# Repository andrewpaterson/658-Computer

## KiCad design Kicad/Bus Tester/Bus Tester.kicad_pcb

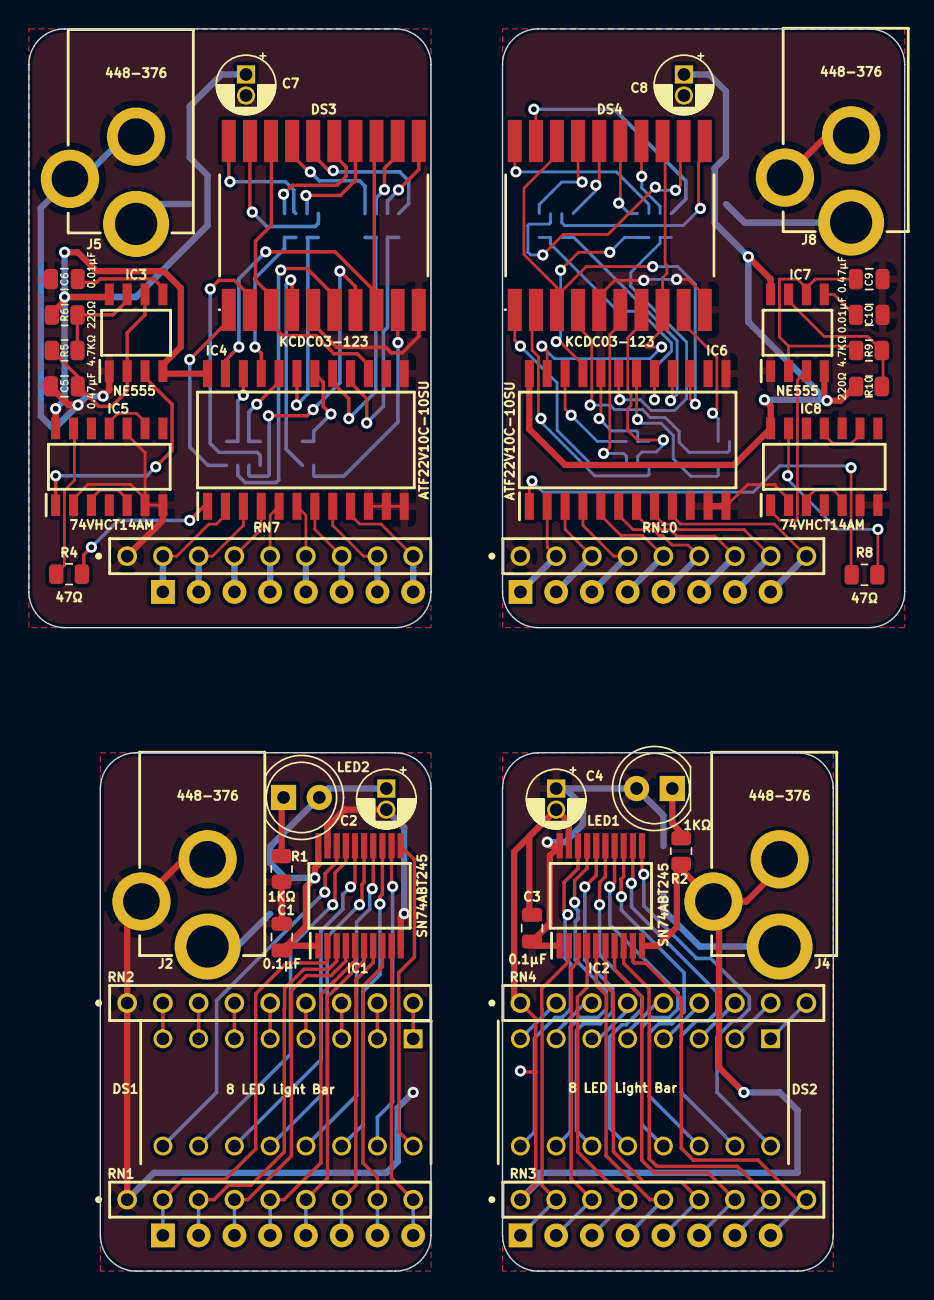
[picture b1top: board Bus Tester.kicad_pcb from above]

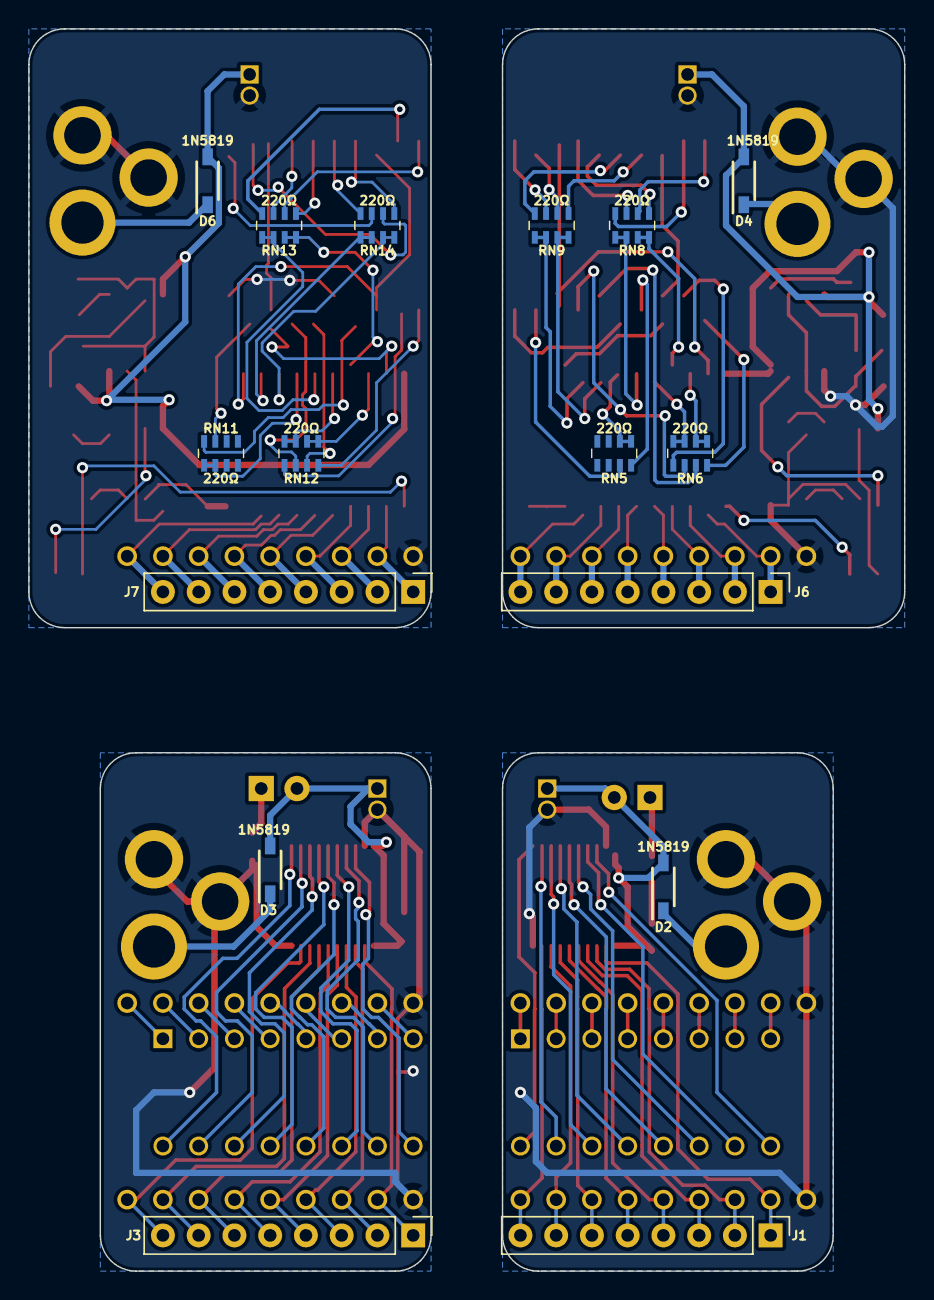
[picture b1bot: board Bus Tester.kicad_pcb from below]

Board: 2 copper layers, 62.2 x 88.3 mm, 58 parts (16 on the bottom side), 140 nets.

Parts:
C1, C3, C5, C6, C9, C10: C_0805
C2, C4, C7, C8: C_Polarized; CP_Radial_D4.0mm_P1.50mm
D2, D3, D4, D6: 1N5819HW-7-F; SOD3716X145N
DS1, DS2: 8 LED Light Bar; DIP8LEDBAR
DS3, DS4: KCDC03-123; KCDC03123
IC1, IC2: SN74ABT245; SOP65P780X200-20N
IC3, IC7: NE555DRG4; SOIC127P600X175-8N
IC4, IC6: ATF22V10C-10SU; SOIC127P1032X265-24N
IC5, IC8: 74VHCT14AM; SOIC127P600X175-14N
J1, J3, J6, J7: Conn_01x08_Male; PinHeader_1x08_P2.54mm_Vertical
J2, J4, J5, J8: 448-376; 448376
LED1, LED2: LED_Small_Filled; LED_D5.0mm
R1, R2, R4, R5, R6, R8, R9, R10: R_0805
RN1, RN3, RN7, RN10: 4609X-101-105LF; 4609X
RN2, RN4: 4609X-101-102LF; 4609X
RN5, RN6, RN8, RN9, RN11, RN12, RN13, RN14: CAY16-221J4LF; CAY1647R0F4LF

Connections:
/Left Handed Bus 7-Segment/5V: C7.1, D4.2, IC3.4 (RESET), IC3.8 (VCC), IC4.24 (5V), IC5.14 (5V), R6.2
/Left Handed Bus 7-Segment/A Seg: IC4.17 (I/O3), RN9.7 (R2), RN9.8 (R1)
/Left Handed Bus 7-Segment/AA: IC4.2 (IN0), J6.1, RN7.2 (R1)
/Left Handed Bus 7-Segment/AB: IC4.3 (IN1), J6.2, RN7.3 (R2)
/Left Handed Bus 7-Segment/AC: IC4.4 (IN2/PD), J6.3, RN7.4 (R3)
/Left Handed Bus 7-Segment/AD: IC4.5 (IN3), J6.4, RN7.5 (R4)
/Left Handed Bus 7-Segment/B Seg: IC4.16 (I/O2), RN9.5 (R4), RN9.6 (R3)
/Left Handed Bus 7-Segment/BA: IC4.6 (IN4), J6.5, RN7.6 (R5)
/Left Handed Bus 7-Segment/BB: IC4.7 (IN5), J6.6, RN7.7 (R6)
/Left Handed Bus 7-Segment/BC: IC4.8 (IN6), J6.7, RN7.8 (R7)
/Left Handed Bus 7-Segment/BD: IC4.9 (IN7), J6.8, RN7.9 (R8)
/Left Handed Bus 7-Segment/C Seg: IC4.18 (I/O4), RN5.1 (R1), RN5.2 (R2)
/Left Handed Bus 7-Segment/Cathode Left: DS3.3 (Cathode_{(Left)}), DS3.18 (Cathode_{(Left)}), IC4.15 (I/O1)
/Left Handed Bus 7-Segment/Cathode Right: DS3.8 (Cathode_{(Right)}), DS3.13 (Cathode_{(Right)}), IC4.23 (I/O9)
/Left Handed Bus 7-Segment/Clock: IC4.1 (CLK/IN), R4.1
/Left Handed Bus 7-Segment/D Seg: IC4.20 (I/O6), RN6.3 (R3), RN6.4 (R4)
/Left Handed Bus 7-Segment/E Seg: IC4.22 (I/O8), RN6.1 (R1), RN6.2 (R2)
/Left Handed Bus 7-Segment/F Seg: IC4.19 (I/O5), RN8.5 (R4), RN8.6 (R3)
/Left Handed Bus 7-Segment/G Seg: IC4.21 (I/O7), RN8.7 (R2), RN8.8 (R1)
/Left Handed Bus 7-Segment/GND: C5.2, C6.2, C7.2, DS3.5 (Dot_{(Left)}), DS3.10 (Dot_{(Right)}), IC3.1 (GND), IC4.10 (IN8), IC4.11 (IN9), IC4.12 (GND), IC4.13 (IN10), IC5.2 (1Y), IC5.6 (3Y), IC5.7 (GND), IC5.10 (5Y), J5.B1 (GND1), J5.C1 (GND2), RN7.1 (PC)
/Left Handed Bus LED/5V: C1.2, C2.1, D2.2, IC1.1 (DIR), IC1.20 (5V), LED2.2 (A)
/Left Handed Bus LED/GND: C1.1, C2.2, IC1.10 (GND), IC1.19 (~OE), J2.B1 (GND1), J2.C1 (GND2), R1.1, RN1.1 (PC), RN2.1 (PC)
/Right Handed Bus 7-Segment/5V: C8.1, D6.2, IC6.24 (5V), IC7.4 (RESET), IC7.8 (VCC), IC8.14 (5V), R10.2
/Right Handed Bus 7-Segment/A Seg: IC6.17 (I/O3), RN14.7 (R2), RN14.8 (R1)
/Right Handed Bus 7-Segment/AA: IC6.2 (IN0), J7.1, RN10.2 (R1)
/Right Handed Bus 7-Segment/AB: IC6.3 (IN1), J7.2, RN10.3 (R2)
/Right Handed Bus 7-Segment/AC: IC6.4 (IN2/PD), J7.3, RN10.4 (R3)
/Right Handed Bus 7-Segment/AD: IC6.5 (IN3), J7.4, RN10.5 (R4)
/Right Handed Bus 7-Segment/B Seg: IC6.16 (I/O2), RN14.5 (R4), RN14.6 (R3)
/Right Handed Bus 7-Segment/BA: IC6.6 (IN4), J7.5, RN10.6 (R5)
/Right Handed Bus 7-Segment/BB: IC6.7 (IN5), J7.6, RN10.7 (R6)
/Right Handed Bus 7-Segment/BC: IC6.8 (IN6), J7.7, RN10.8 (R7)
/Right Handed Bus 7-Segment/BD: IC6.9 (IN7), J7.8, RN10.9 (R8)
/Right Handed Bus 7-Segment/C Seg: IC6.18 (I/O4), RN11.1 (R1), RN11.2 (R2)
/Right Handed Bus 7-Segment/Cathode Left: DS4.3 (Cathode_{(Left)}), DS4.18 (Cathode_{(Left)}), IC6.15 (I/O1)
/Right Handed Bus 7-Segment/Cathode Right: DS4.8 (Cathode_{(Right)}), DS4.13 (Cathode_{(Right)}), IC6.23 (I/O9)
/Right Handed Bus 7-Segment/Clock: IC6.1 (CLK/IN), R8.1
/Right Handed Bus 7-Segment/D Seg: IC6.20 (I/O6), RN12.3 (R3), RN12.4 (R4)
/Right Handed Bus 7-Segment/E Seg: IC6.22 (I/O8), RN12.1 (R1), RN12.2 (R2)
/Right Handed Bus 7-Segment/F Seg: IC6.19 (I/O5), RN13.5 (R4), RN13.6 (R3)
/Right Handed Bus 7-Segment/G Seg: IC6.21 (I/O7), RN13.7 (R2), RN13.8 (R1)
/Right Handed Bus 7-Segment/GND: C8.2, C9.2, C10.2, DS4.5 (Dot_{(Left)}), DS4.10 (Dot_{(Right)}), IC6.10 (IN8), IC6.11 (IN9), IC6.12 (GND), IC6.13 (IN10), IC7.1 (GND), IC8.2 (1Y), IC8.6 (3Y), IC8.7 (GND), IC8.10 (5Y), J8.B1 (GND1), J8.C1 (GND2), RN10.1 (PC)
/Right Handed Bus LED/5V: C3.2, C4.1, D3.2, IC2.1 (DIR), IC2.20 (5V), LED1.2 (A)
/Right Handed Bus LED/GND: C3.1, C4.2, IC2.10 (GND), IC2.19 (~OE), J4.B1 (GND1), J4.C1 (GND2), R2.1, RN3.1 (PC), RN4.1 (PC)
unnamed: C5.1, IC3.2 (TRIG), IC3.6 (THRES), R5.1
unnamed: C6.1, IC3.5 (CONT)
unnamed: C9.1, IC7.2 (TRIG), IC7.6 (THRES), R9.1
unnamed: C10.1, IC7.5 (CONT)
unnamed: D2.1, J2.A1 (VCC)
unnamed: D3.1, J4.A1 (VCC)
unnamed: DS1.1 (ANODE_A), RN2.9 (R8)
unnamed: DS1.2 (ANODE_B), RN2.8 (R7)
unnamed: DS1.3 (ANODE_C), RN2.7 (R6)
unnamed: DS1.4 (ANODE_D), RN2.6 (R5)
unnamed: DS1.5 (ANODE_E), RN2.5 (R4)
unnamed: DS1.6 (ANODE_F), RN2.4 (R3)
unnamed: DS1.7 (ANODE_G), RN2.3 (R2)
unnamed: DS1.8 (ANODE_H), RN2.2 (R1)
unnamed: DS1.9 (CATHODE_H), IC1.18 (B1)
unnamed: DS1.10 (CATHODE_G), IC1.17 (B2)
unnamed: DS1.11 (CATHODE_F), IC1.16 (B3)
unnamed: DS1.12 (CATHODE_E), IC1.15 (B4)
unnamed: DS1.13 (CATHODE_D), IC1.14 (B5)
unnamed: DS1.14 (CATHODE_C), IC1.13 (B6)
unnamed: DS1.15 (CATHODE_B), IC1.12 (B7)
unnamed: DS1.16 (CATHODE_A), IC1.11 (B8)
unnamed: DS2.1 (ANODE_A), RN4.9 (R8)
unnamed: DS2.2 (ANODE_B), RN4.8 (R7)
unnamed: DS2.3 (ANODE_C), RN4.7 (R6)
unnamed: DS2.4 (ANODE_D), RN4.6 (R5)
unnamed: DS2.5 (ANODE_E), RN4.5 (R4)
unnamed: DS2.6 (ANODE_F), RN4.4 (R3)
unnamed: DS2.7 (ANODE_G), RN4.3 (R2)
unnamed: DS2.8 (ANODE_H), RN4.2 (R1)
unnamed: DS2.9 (CATHODE_H), IC2.18 (B1)
unnamed: DS2.10 (CATHODE_G), IC2.17 (B2)
unnamed: DS2.11 (CATHODE_F), IC2.16 (B3)
unnamed: DS2.12 (CATHODE_E), IC2.15 (B4)
unnamed: DS2.13 (CATHODE_D), IC2.14 (B5)
unnamed: DS2.14 (CATHODE_C), IC2.13 (B6)
unnamed: DS2.15 (CATHODE_B), IC2.12 (B7)
unnamed: DS2.16 (CATHODE_A), IC2.11 (B8)
unnamed: DS3.1 (E-Seg_{(Left)}), RN6.8 (R1)
unnamed: DS3.2 (D-Seg_{(Left)}), RN6.5 (R4)
unnamed: DS3.4 (C-Seg_{(Left)}), RN5.8 (R1)
unnamed: DS3.6 (E-Seg_{(Right)}), RN6.7 (R2)
unnamed: DS3.7 (D-Seg_{(Right)}), RN6.6 (R3)
unnamed: DS3.9 (C-Seg_{(Right)}), RN5.7 (R2)
unnamed: DS3.11 (B-Seg_{(Right)}), RN9.3 (R3)
unnamed: DS3.12 (A-Seg_{(Right)}), RN9.2 (R2)
unnamed: DS3.14 (F-Seg_{(Right)}), RN8.3 (R3)
unnamed: DS3.15 (G-Seg_{(Right)}), RN8.1 (R1)
unnamed: DS3.16 (B-Seg_{(Left)}), RN9.4 (R4)
unnamed: DS3.17 (A-Seg_{(Left)}), RN9.1 (R1)
unnamed: DS3.19 (F-Seg_{(Left)}), RN8.4 (R4)
unnamed: DS3.20 (G-Seg_{(Left)}), RN8.2 (R2)
unnamed: DS4.1 (E-Seg_{(Left)}), RN12.8 (R1)
unnamed: DS4.2 (D-Seg_{(Left)}), RN12.5 (R4)
unnamed: DS4.4 (C-Seg_{(Left)}), RN11.8 (R1)
unnamed: DS4.6 (E-Seg_{(Right)}), RN12.7 (R2)
unnamed: DS4.7 (D-Seg_{(Right)}), RN12.6 (R3)
unnamed: DS4.9 (C-Seg_{(Right)}), RN11.7 (R2)
unnamed: DS4.11 (B-Seg_{(Right)}), RN14.3 (R3)
unnamed: DS4.12 (A-Seg_{(Right)}), RN14.2 (R2)
unnamed: DS4.14 (F-Seg_{(Right)}), RN13.3 (R3)
unnamed: DS4.15 (G-Seg_{(Right)}), RN13.1 (R1)
unnamed: DS4.16 (B-Seg_{(Left)}), RN14.4 (R4)
unnamed: DS4.17 (A-Seg_{(Left)}), RN14.1 (R1)
unnamed: DS4.19 (F-Seg_{(Left)}), RN13.4 (R4)
unnamed: DS4.20 (G-Seg_{(Left)}), RN13.2 (R2)
unnamed: IC1.2 (A1), J1.1, RN1.2 (R1)
unnamed: IC1.3 (A2), J1.2, RN1.3 (R2)
unnamed: IC1.4 (A3), J1.3, RN1.4 (R3)
unnamed: IC1.5 (A4), J1.4, RN1.5 (R4)
unnamed: IC1.6 (A5), J1.5, RN1.6 (R5)
unnamed: IC1.7 (A6), J1.6, RN1.7 (R6)
unnamed: IC1.8 (A7), J1.7, RN1.8 (R7)
unnamed: IC1.9 (A8), J1.8, RN1.9 (R8)
unnamed: IC2.2 (A1), J3.1, RN3.2 (R1)
unnamed: IC2.3 (A2), J3.2, RN3.3 (R2)
unnamed: IC2.4 (A3), J3.3, RN3.4 (R3)
unnamed: IC2.5 (A4), J3.4, RN3.5 (R4)
unnamed: IC2.6 (A5), J3.5, RN3.6 (R5)
unnamed: IC2.7 (A6), J3.6, RN3.7 (R6)
unnamed: IC2.8 (A7), J3.7, RN3.8 (R7)
unnamed: IC2.9 (A8), J3.8, RN3.9 (R8)
unnamed: IC3.3 (OUT), IC5.1 (1A)
unnamed: IC3.7 (DISCH), R5.2, R6.1
unnamed: IC5.3 (2A), IC5.5 (3A)
unnamed: IC5.9 (4A), IC5.11 (5A)
unnamed: IC5.13 (6A), R4.2
unnamed: IC7.3 (OUT), IC8.1 (1A)
unnamed: IC7.7 (DISCH), R9.2, R10.1
unnamed: IC8.3 (2A), IC8.5 (3A)
unnamed: IC8.9 (4A), IC8.11 (5A)
unnamed: IC8.13 (6A), R8.2
unnamed: D4.1, J5.A1 (VCC)
unnamed: D6.1, J8.A1 (VCC)
unnamed: LED1.1 (K), R2.2
unnamed: LED2.1 (K), R1.2

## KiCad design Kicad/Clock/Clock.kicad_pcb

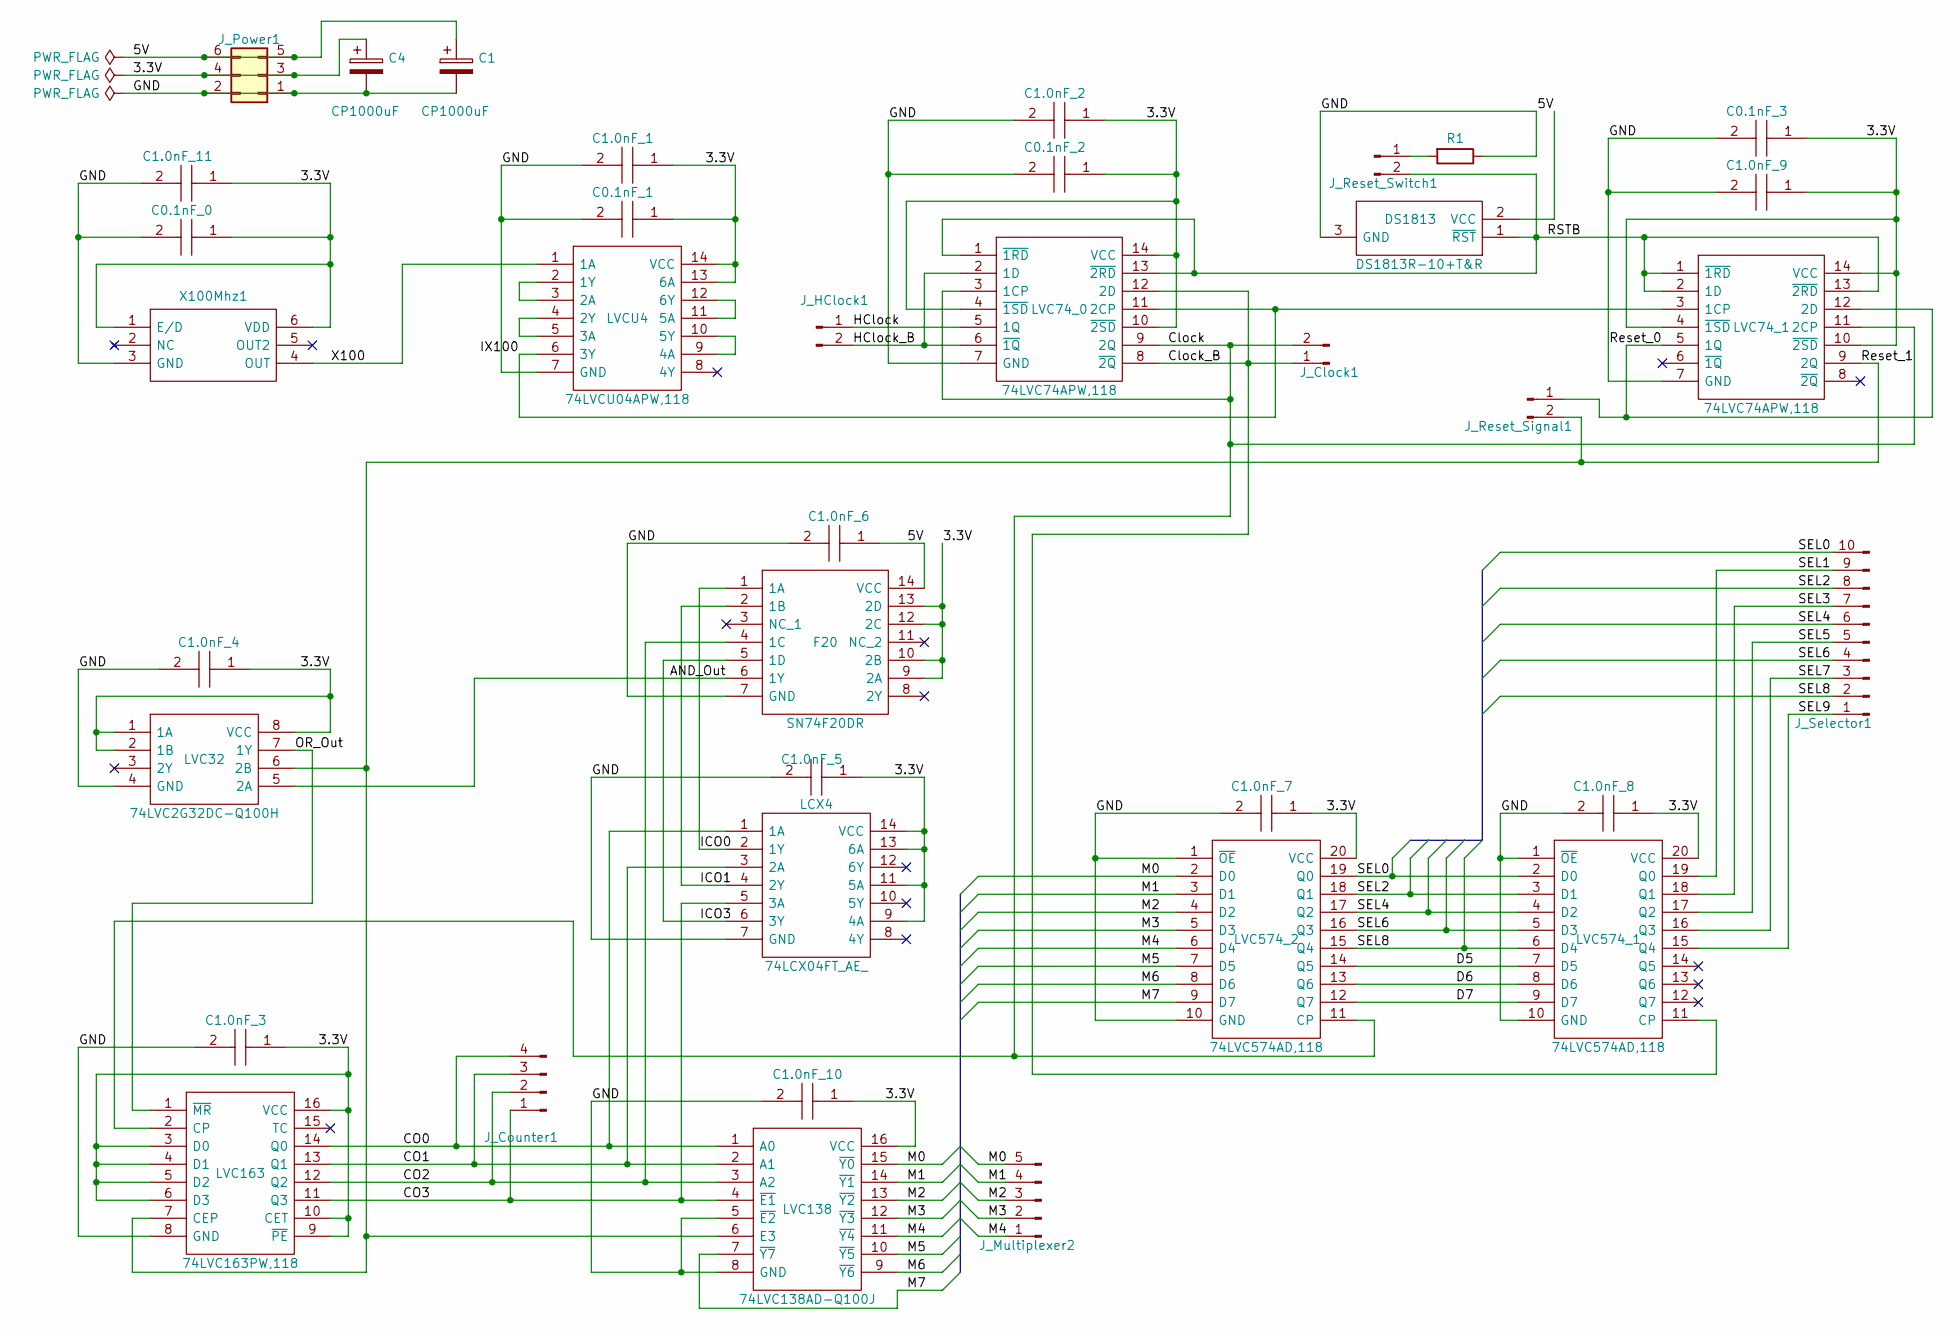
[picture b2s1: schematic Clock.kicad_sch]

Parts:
C0.1nF_0, C0.1nF_1, C0.1nF_2, C0.1nF_3: 885012207027; CAPC2012X90N; Mouser Part Number 710-885012207027
C1, C4: CP1000uF; CP_Radial_D7.5mm_P2.50mm
C1.0nF_1, C1.0nF_2, C1.0nF_3, C1.0nF_4, C1.0nF_5, C1.0nF_6, C1.0nF_7, C1.0nF_8, C1.0nF_9, C1.0nF_10, C1.0nF_11: 885012207033; CAPC2012X90N; Mouser Part Number 710-885012207033
DS1813: DS1813R-10+T&R; SOT95P237X112-3N; Mouser Part Number 700-DS1813R-10T&R
F20: SN74F20DR; SOIC127P600X175-14N; Mouser Part Number 595-SN74F20DR
J_Clock1: Conn_01x02_Male; PinHeader_1x02_P2.54mm_Vertical
J_Counter1: Conn_01x05_Male; PinHeader_1x04_P2.54mm_Vertical
J_HClock1: Conn_01x02_Male; PinHeader_1x02_P2.54mm_Vertical
J_Multiplexer2: Conn_01x05_Male; PinHeader_1x05_P2.54mm_Vertical
J_Power1: Conn_02x03; PinSocket_2x03_P2.54mm_Vertical
J_Reset_Signal1: Conn_01x02_Male; PinHeader_1x02_P2.54mm_Vertical
J_Reset_Switch1: Conn_01x02_Male; PinHeader_1x02_P2.54mm_Vertical
J_Selector1: Conn_01x10_Male; PinHeader_1x10_P2.54mm_Vertical
LCX4: 74LCX04FT_AE_; SOP65P640X120-14N; Mouser Part Number 757-74LCX04FTAE
LVC32: 74LVC2G32DC-Q100H; SOP50P310X100-8N; Mouser Part Number 771-74LVC2G32DCQ100H
LVC74_0, LVC74_1: 74LVC74APW,118; SOP65P640X110-14N; Mouser Part Number 771-74LVC74APW-T
LVC138: 74LVC138AD-Q100J; SOIC127P600X175-16N; Mouser Part Number 771-74LVC138ADQ100J
LVC163: 74LVC163PW,118; SOP65P640X110-16N; Mouser Part Number 771-74LVC163PW-T
LVC574_1, LVC574_2: 74LVC574AD,118; SOIC127P1032X265-20N; Mouser Part Number 771-74LVC574AD-T
LVCU4: 74LVCU04APW,118; SOP65P640X110-14N; Mouser Part Number 771-LVCU04APW118
R1: R; R_Axial_DIN0204_L3.6mm_D1.6mm_P7.62mm_Horizontal
X100Mhz1: XLH735100.000000I; XLH735100000000I; Mouser Part Number 972-XLH735100000000I

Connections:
/3.3V: C0.1nF_0.1, C0.1nF_1.1, C0.1nF_2.1, C0.1nF_3.1, C1.0nF_1.1, C1.0nF_2.1, C1.0nF_3.1, C1.0nF_4.1, C1.0nF_5.1, C1.0nF_7.1, C1.0nF_8.1, C1.0nF_9.1, C1.0nF_10.1, C1.0nF_11.1, C4.1, F20.9 (2A), F20.10 (2B), F20.12 (2C), F20.13 (2D), J_Power1.3, J_Power1.4, LCX4.9 (4A), LCX4.11 (5A), LCX4.13 (6A), LCX4.14 (VCC), LVC32.1 (1A), LVC32.2 (1B), LVC32.8 (VCC), LVC74_0.4 (~1SD), LVC74_0.10 (~2SD), LVC74_0.14 (VCC), LVC74_1.4 (~1SD), LVC74_1.10 (~2SD), LVC74_1.14 (VCC), LVC138.16 (VCC), LVC163.3 (D0), LVC163.4 (D1), LVC163.5 (D2), LVC163.6 (D3), LVC163.9 (~PE), LVC163.10 (CET), LVC163.16 (VCC), LVC574_1.20 (VCC), LVC574_2.20 (VCC), LVCU4.13 (6A), LVCU4.14 (VCC), X100Mhz1.1 (E/D), X100Mhz1.6 (VDD)
/5V: C1.1, C1.0nF_6.1, DS1813.2 (VCC), F20.14 (VCC), J_Power1.5, J_Power1.6
/AND_Out: F20.6 (1Y), LVC32.5 (2A)
/CO0: J_Counter1.4, LCX4.1 (1A), LVC138.1 (A0), LVC163.14 (Q0)
/CO1: J_Counter1.3, LCX4.3 (2A), LVC138.2 (A1), LVC163.13 (Q1)
/CO2: F20.4 (1C), J_Counter1.2, LVC138.3 (A2), LVC163.12 (Q2)
/CO3: J_Counter1.1, LCX4.5 (3A), LVC138.4 (~E1), LVC163.11 (Q3)
/Clock: J_Clock1.2, LVC74_0.3 (1CP), LVC74_0.9 (2Q), LVC74_1.11 (2CP), LVC163.2 (CP), LVC574_2.11 (CP)
/Clock_B: J_Clock1.1, LVC74_0.8 (~2Q), LVC74_0.12 (2D), LVC574_1.11 (CP)
/D5: LVC574_1.7 (D5), LVC574_2.14 (Q5)
/D6: LVC574_1.8 (D6), LVC574_2.13 (Q6)
/D7: LVC574_1.9 (D7), LVC574_2.12 (Q7)
/GND: C0.1nF_0.2, C0.1nF_1.2, C0.1nF_2.2, C0.1nF_3.2, C1.2, C1.0nF_1.2, C1.0nF_2.2, C1.0nF_3.2, C1.0nF_4.2, C1.0nF_5.2, C1.0nF_6.2, C1.0nF_7.2, C1.0nF_8.2, C1.0nF_9.2, C1.0nF_10.2, C1.0nF_11.2, C4.2, DS1813.3 (GND), F20.7 (GND), J_Power1.1, J_Power1.2, LCX4.7 (GND), LVC32.4 (GND), LVC74_0.7 (GND), LVC74_1.7 (GND), LVC138.5 (~E2), LVC138.8 (GND), LVC163.8 (GND), LVC574_1.1 (~OE), LVC574_1.10 (GND), LVC574_2.1 (~OE), LVC574_2.10 (GND), LVCU4.7 (GND), R1.1, X100Mhz1.3 (GND)
/HClock: J_HClock1.1, LVC74_0.5 (1Q)
/HClock_B: J_HClock1.2, LVC74_0.2 (1D), LVC74_0.6 (~1Q)
/ICO0: F20.1 (1A), LCX4.2 (1Y)
/ICO1: F20.2 (1B), LCX4.4 (2Y)
/ICO3: F20.5 (1D), LCX4.6 (3Y)
/IX100: LVC74_0.11 (2CP), LVC74_1.3 (1CP), LVCU4.6 (3Y)
/M0: J_Multiplexer2.5, LVC138.15 (~Y0), LVC574_2.2 (D0)
/M1: J_Multiplexer2.4, LVC138.14 (~Y1), LVC574_2.3 (D1)
/M2: J_Multiplexer2.3, LVC138.13 (~Y2), LVC574_2.4 (D2)
/M3: J_Multiplexer2.2, LVC138.12 (~Y3), LVC574_2.5 (D3)
/M4: J_Multiplexer2.1, LVC138.11 (~Y4), LVC574_2.6 (D4)
/M5: LVC138.10 (~Y5), LVC574_2.7 (D5)
/M6: LVC138.9 (~Y6), LVC574_2.8 (D6)
/M7: LVC138.7 (~Y7), LVC574_2.9 (D7)
/OR_Out: LVC32.7 (1Y), LVC163.1 (~MR)
/RSTB: DS1813.1 (~RST), J_Reset_Switch1.2, LVC74_0.1 (~1RD), LVC74_0.13 (~2RD), LVC74_1.1 (~1RD), LVC74_1.2 (1D), LVC74_1.13 (~2RD)
/Reset_0: J_Reset_Signal1.1, LVC74_1.5 (1Q), LVC74_1.12 (2D)
/Reset_1: J_Reset_Signal1.2, LVC32.6 (2B), LVC74_1.9 (2Q), LVC138.6 (E3), LVC163.7 (CEP)
/SEL0: J_Selector1.10, LVC574_1.2 (D0), LVC574_2.19 (Q0)
/SEL1: J_Selector1.9, LVC574_1.19 (Q0)
/SEL2: J_Selector1.8, LVC574_1.3 (D1), LVC574_2.18 (Q1)
/SEL3: J_Selector1.7, LVC574_1.18 (Q1)
/SEL4: J_Selector1.6, LVC574_1.4 (D2), LVC574_2.17 (Q2)
/SEL5: J_Selector1.5, LVC574_1.17 (Q2)
/SEL6: J_Selector1.4, LVC574_1.5 (D3), LVC574_2.16 (Q3)
/SEL7: J_Selector1.3, LVC574_1.16 (Q3)
/SEL8: J_Selector1.2, LVC574_1.6 (D4), LVC574_2.15 (Q4)
/SEL9: J_Selector1.1, LVC574_1.15 (Q4)
/X100: LVCU4.1 (1A), X100Mhz1.4 (OUT)
unnamed: J_Reset_Switch1.1, R1.2
unnamed: LVCU4.2 (1Y), LVCU4.3 (2A)
unnamed: LVCU4.4 (2Y), LVCU4.5 (3A)
unnamed: LVCU4.9 (4A), LVCU4.10 (5Y)
unnamed: LVCU4.11 (5A), LVCU4.12 (6Y)

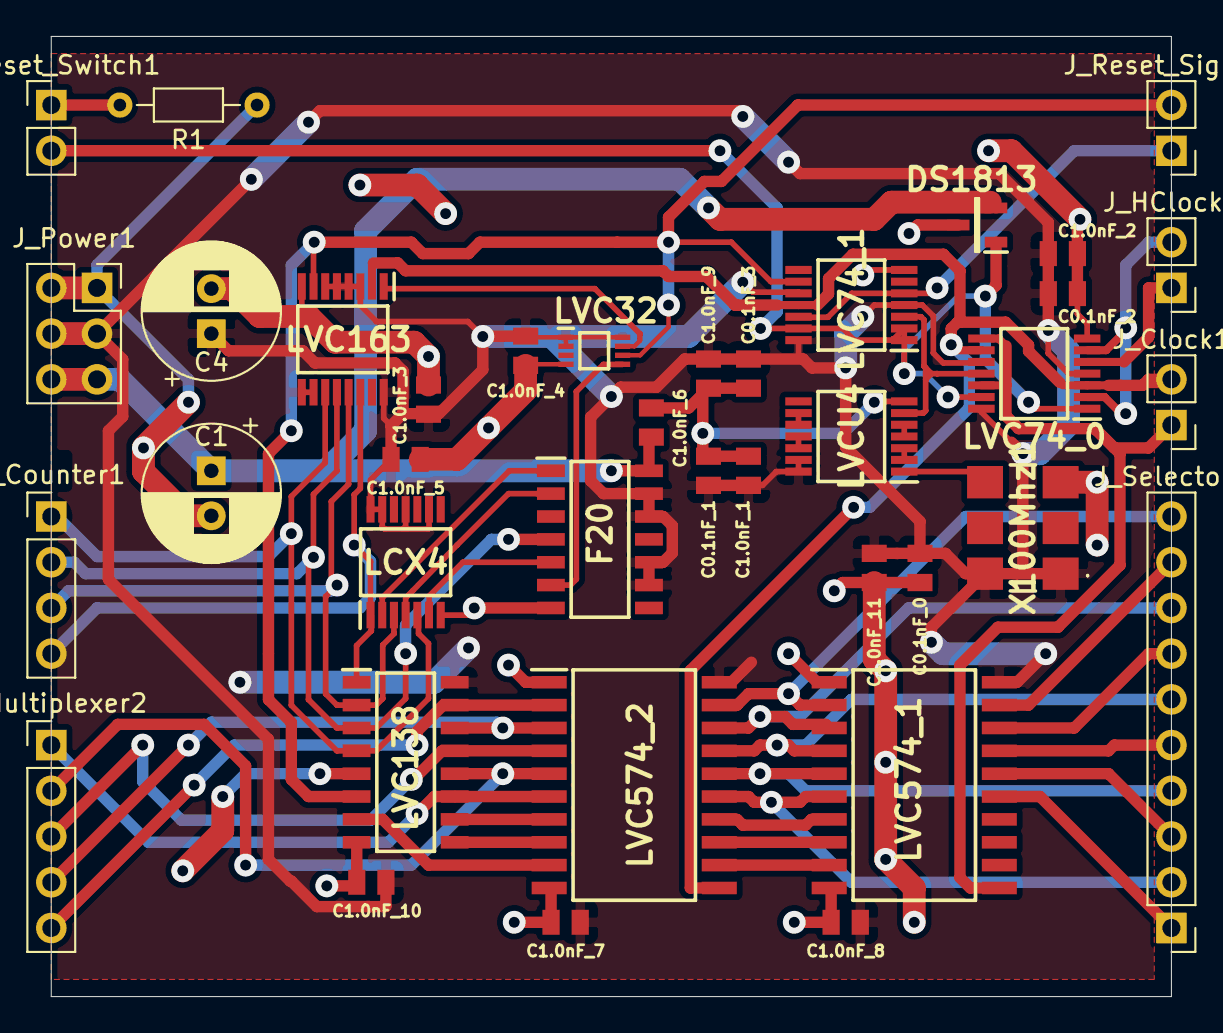
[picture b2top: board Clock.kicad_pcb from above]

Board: 2 copper layers, 62.2 x 53.3 mm, 38 parts (0 on the bottom side), 47 nets.
